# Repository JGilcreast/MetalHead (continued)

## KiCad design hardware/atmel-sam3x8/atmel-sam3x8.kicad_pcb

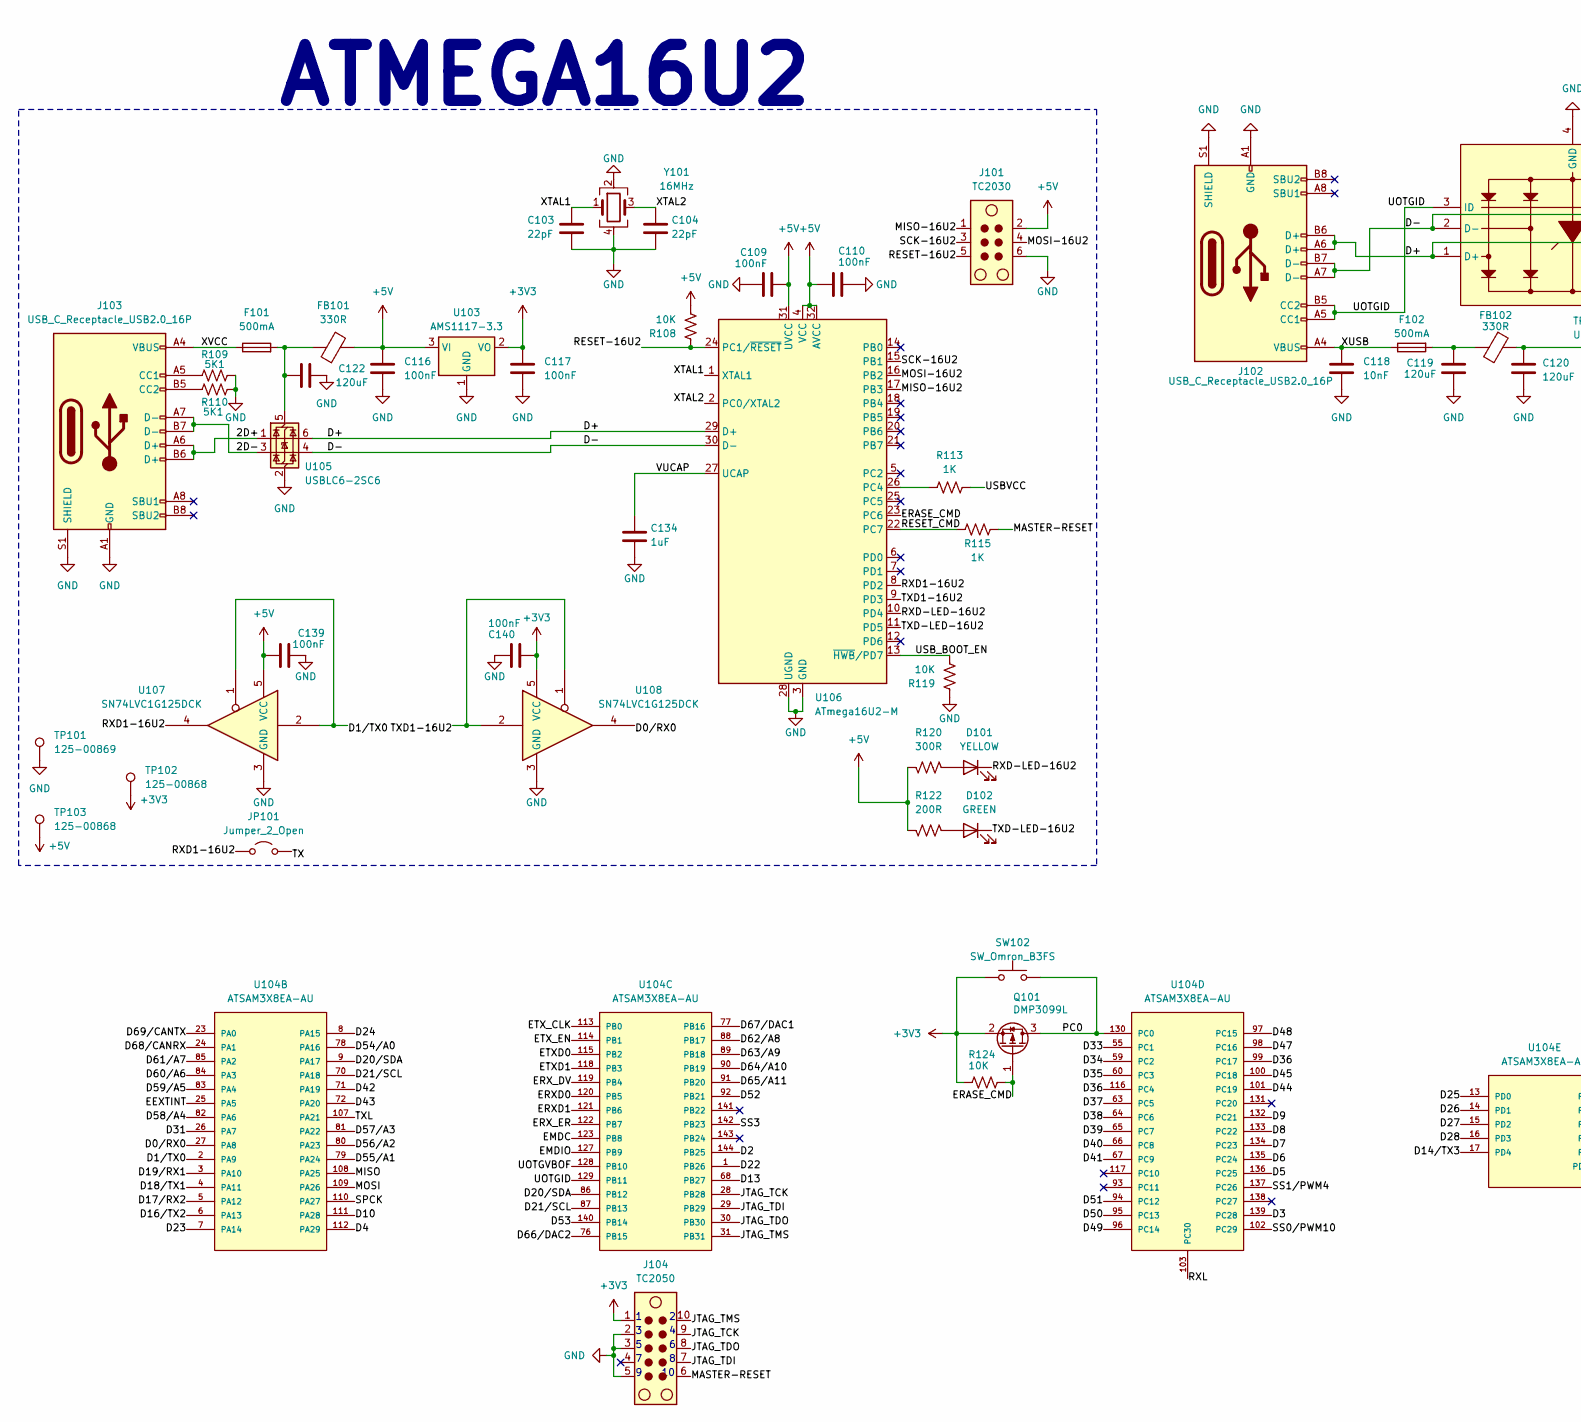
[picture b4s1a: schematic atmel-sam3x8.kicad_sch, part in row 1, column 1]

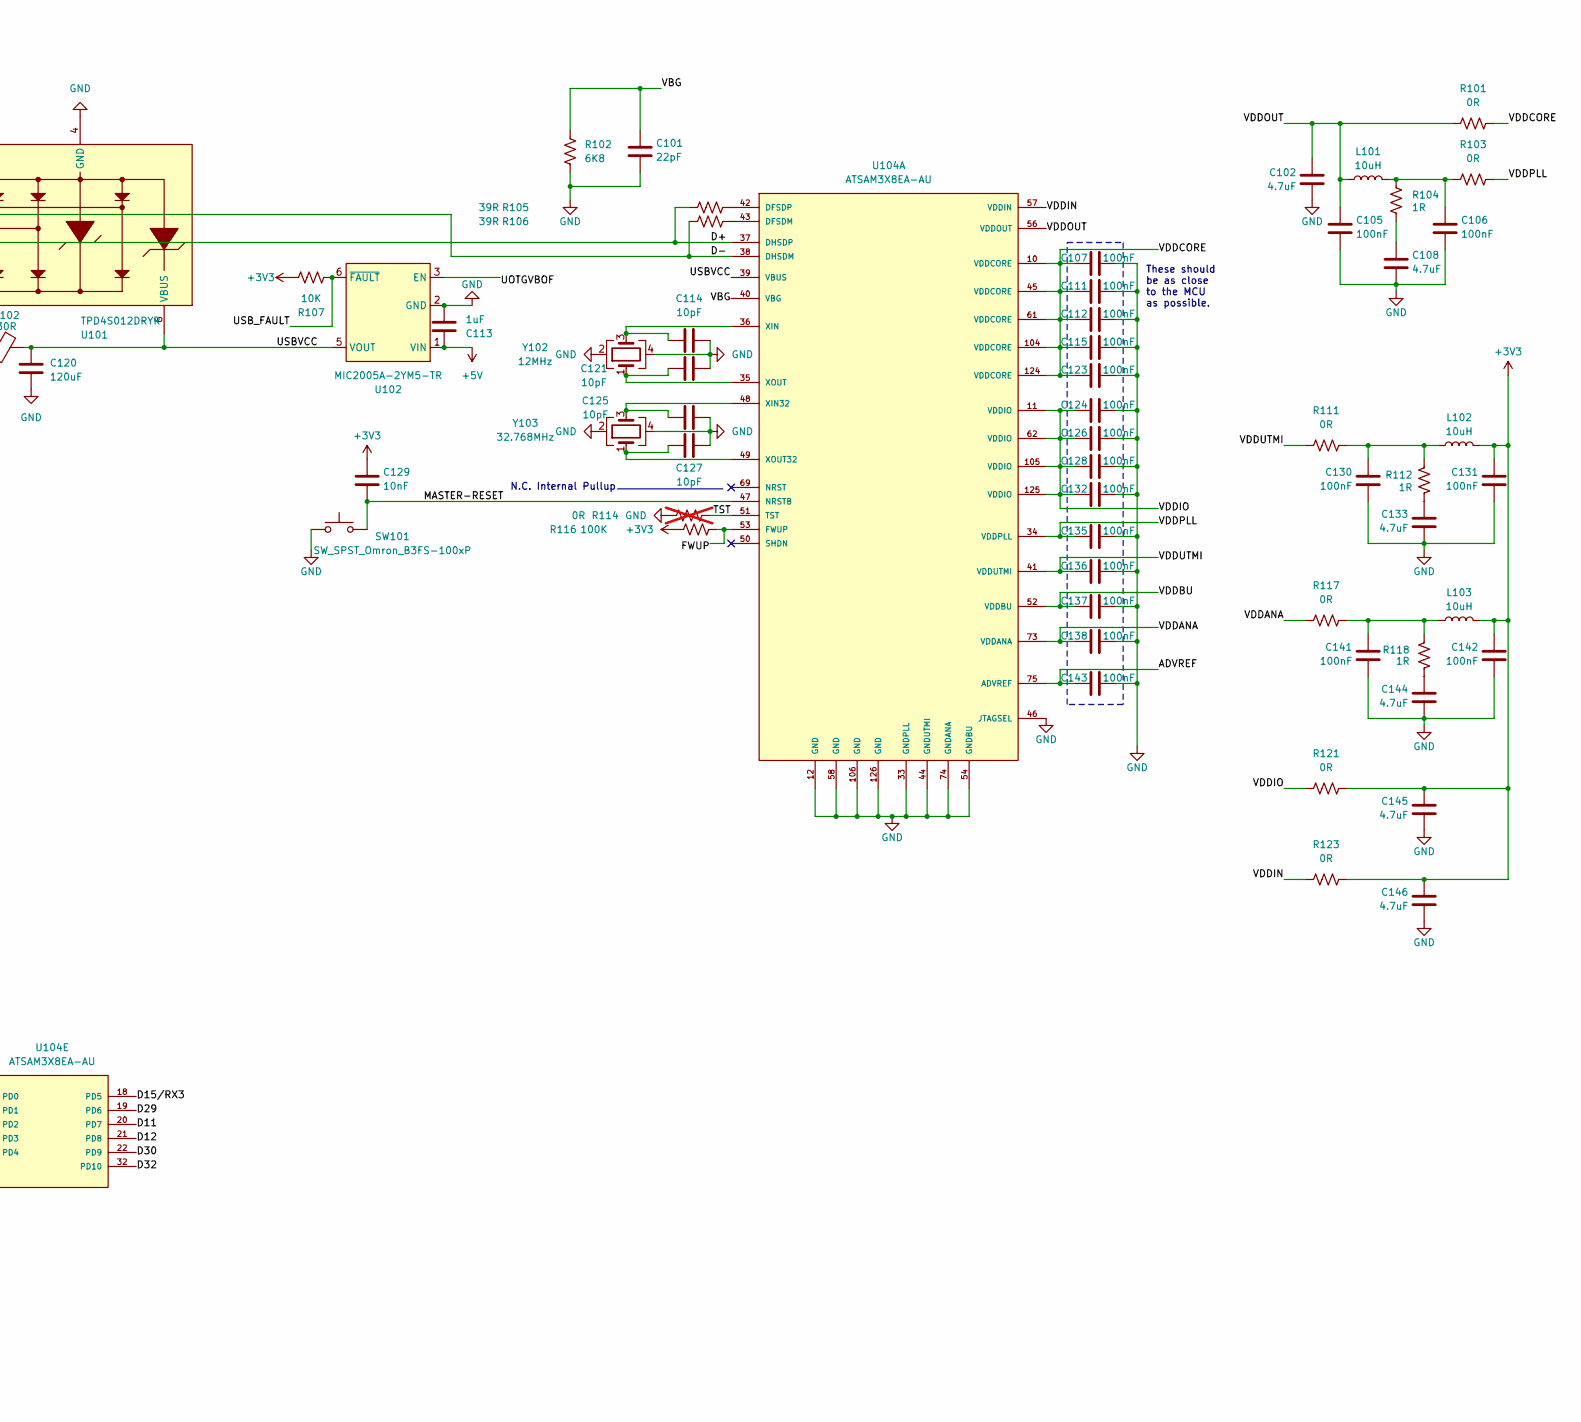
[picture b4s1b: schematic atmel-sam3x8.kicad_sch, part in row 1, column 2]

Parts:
C101, C103, C104: 22pF; C_0805_2012Metric
C102, C108, C133, C144, C145, C146: 4.7uF; C_0805_2012Metric
C105, C106, C107, C109, C110, C111, C112, C115, C116, C117, C123, C124, C126, C128, C130, C131, C132, C135, C136, C137, C138, C139, C140, C141, C142, C143: 100nF; C_0805_2012Metric
C113, C134: 1uF; C_0805_2012Metric
C114, C121, C125, C127: 10pF; C_0805_2012Metric
C118, C129: 10nF; C_0805_2012Metric
C119, C120, C122: 120uF; C_0805_2012Metric
D101: YELLOW; LED_1206_3216Metric
D102: GREEN; LED_1206_3216Metric
F101, F102: 500mA; Fuse_0805_2012Metric
FB101, FB102: 330R; L_0805_2012Metric
J101: TC2030; Tag-Connect_TC2030-IDC-NL_2x03_P1.27mm_Vertical
J102, J103: USB_C_Receptacle_USB2.0_16P; USB_C_Receptacle_G-Switch_GT-USB-7010ASV
J104: TC2050; Tag-Connect_TC2050-IDC-FP_2x05_P1.27mm_Vertical
JP101: Jumper_2_Open; TestPoint_2Pads_Pitch2.54mm_Drill0.8mm
L101, L102, L103: 10uH; L_0805_2012Metric
Q101: DMP3099L; SOT-23-3
R101, R103, R111, R117, R121, R123: 0R; R_0805_2012Metric
R102: 6K8; R_0805_2012Metric
R104, R112, R118: 1R; R_0805_2012Metric
R105, R106: 39R; R_0805_2012Metric
R107, R108, R119, R124: 10K; R_0805_2012Metric
R109, R110: 5K1; R_0805_2012Metric
R113, R115: 1K; R_0805_2012Metric
R114: 0R; R_0805_2012Metric; not fitted
R116: 100K; R_0805_2012Metric
R120: 300R; R_0805_2012Metric
R122: 200R; R_0805_2012Metric
SW101: SW_SPST_Omron_B3FS-100xP; SW_SPST_EVQPE1
SW102: SW_Omron_B3FS; SW_SPST_Omron_B3FS-100xP
TP101: 125-00869; TestPoint_Keystone_5000-5004_Miniature
TP102, TP103: 125-00868; TestPoint_Keystone_5000-5004_Miniature
U101: TPD4S012DRYR; Mouser Part Number 595-TPD4S012DRYR
U102: MIC2005A-2YM5-TR; SOT95P280X145-5N; Mouser Part Number 998-MIC2005A-1YM5TR
U103: AMS1117-3.3; SOT-223-3_TabPin2
U104: ATSAM3X8EA-AU; QFP50P2200X2200X145-144N; PARTREV 11057C
U105: USBLC6-2SC6; SOT-23-6
U106: ATmega16U2-M; QFN-32-1EP_5x5mm_P0.5mm_EP3.6x3.6mm_ThermalVias
U107, U108: SN74LVC1G125DCK; Texas_R-PDSO-G5_DCK-5
Y101: 16MHz; Crystal_SMD_3225-4Pin_3.2x2.5mm
Y102: 12MHz; Crystal_SMD_3225-4Pin_3.2x2.5mm
Y103: 32.768MHz; Crystal_SMD_3225-4Pin_3.2x2.5mm

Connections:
+3V3: C117.1, C129.1, C131.1, C140.1, C142.1, C145.1, C146.1, J104.1, L102.1, L103.1, Q101.2 (S), R107.2, R116.1, R121.2, R123.2, R124.2, SW102.1, TP102.1, U103.2 (VO), U108.5 (VCC)
+5V: C109.1, C110.1, C113.1, C116.1, C139.1, FB101.2, J101.2, R108.2, R120.2, R122.2, TP103.1, U102.1 (VIN), U103.3 (VI), U106.4 (VCC), U106.31 (UVCC), U106.32 (AVCC), U107.5 (VCC)
/2D+: J103.A6 (D+), J103.B6 (D+), U105.1 (I/O1)
/2D-: J103.A7 (D-), J103.B7 (D-), U105.3 (I/O2)
/ADVREF: C143.1, U104.75 (ADVREF)
/D0/RX0: U104.27 (PA8), U108.4
/D1/TX0: U104.2 (PA9), U107.1, U107.2
/D2: U104.144 (PB25)
/D3: U104.139 (PC28)
/D4: U104.112 (PA29)
/D5: U104.136 (PC25)
/D6: U104.135 (PC24)
/D7: U104.134 (PC23)
/D8: U104.133 (PC22)
/D9: U104.132 (PC21)
/D10: U104.111 (PA28)
/D11: U104.20 (PD7)
/D12: U104.21 (PD8)
/D13: U104.68 (PB27)
/D14/TX3: U104.17 (PD4)
/D15/RX3: U104.18 (PD5)
/D16/TX2: U104.6 (PA13)
/D17/RX2: U104.5 (PA12)
/D18/TX1: U104.4 (PA11)
/D19/RX1: U104.3 (PA10)
/D20/SDA: U104.9 (PA17), U104.86 (PB12)
/D21/SCL: U104.70 (PA18), U104.87 (PB13)
/D22: U104.1 (PB26)
/D23: U104.7 (PA14)
/D24: U104.8 (PA15)
/D25: U104.13 (PD0)
/D26: U104.14 (PD1)
/D27: U104.15 (PD2)
/D28: U104.16 (PD3)
/D29: U104.19 (PD6)
/D30: U104.22 (PD9)
/D31: U104.26 (PA7)
/D32: U104.32 (PD10)
/D33: U104.55 (PC1)
/D34: U104.59 (PC2)
/D35: U104.60 (PC3)
/D36: U104.99 (PC17), U104.116 (PC4)
/D37: U104.63 (PC5)
/D38: U104.64 (PC6)
/D39: U104.65 (PC7)
/D40: U104.66 (PC8)
/D41: U104.67 (PC9)
/D42: U104.71 (PA19)
/D43: U104.72 (PA20)
/D44: U104.101 (PC19)
/D45: U104.100 (PC18)
/D47: U104.98 (PC16)
/D48: U104.97 (PC15)
/D49: U104.96 (PC14)
/D50: U104.95 (PC13)
/D51: U104.94 (PC12)
/D52: U104.92 (PB21)
/D53: U104.140 (PB14)
/D54/A0: U104.78 (PA16)
/D55/A1: U104.79 (PA24)
/D56/A2: U104.80 (PA23)
/D57/A3: U104.81 (PA22)
/D58/A4: U104.82 (PA6)
/D59/A5: U104.83 (PA4)
/D60/A6: U104.84 (PA3)
/D61/A7: U104.85 (PA2)
/D62/A8: U104.88 (PB17)
/D63/A9: U104.89 (PB18)
/D64/A10: U104.90 (PB19)
/D65/A11: U104.91 (PB20)
/D66/DAC2: U104.76 (PB15)
/D67/DAC1: U104.77 (PB16)
/D68/CANRX: U104.24 (PA1)
/D69/CANTX: U104.23 (PA0)
/D+: J102.A5 (CC1), J102.A6 (D+), J102.A7 (D-), J102.B5 (CC2), J102.B6 (D+), J102.B7 (D-), R105.2, R106.2, U101.1 (D+), U101.2 (D-), U101.3 (ID), U104.37 (DHSDP), U104.38 (DHSDM), U104.129 (PB11), U105.4 (I/O2), U105.6 (I/O1), U106.29 (D+), U106.30 (D-)
/EEXTINT: U104.25 (PA5)
/EMDC: U104.123 (PB8)
/EMDIO: U104.127 (PB9)
/ERASE_CMD: Q101.1 (G), R124.1, U106.23 (PC6)
/ERXD0: U104.120 (PB5)
/ERXD1: U104.121 (PB6)
/ERX_DV: U104.119 (PB4)
/ERX_ER: U104.122 (PB7)
/ETXD0: U104.115 (PB2)
/ETXD1: U104.118 (PB3)
/ETX_CLK: U104.113 (PB0)
/ETX_EN: U104.114 (PB1)
/FWUP: R116.2, U104.53 (FWUP)
/JTAG_TCK: J104.9, U104.28 (PB28)
/JTAG_TDI: J104.7, U104.29 (PB29)
/JTAG_TDO: J104.8, U104.30 (PB30)
/JTAG_TMS: J104.10, U104.31 (PB31)
/MASTER-RESET: C129.2, J104.6, R115.2, SW101.2, U104.47 (NRSTB)
/MISO: U104.108 (PA25)
/MISO-16U2: J101.1, U106.17 (PB3)
/MOSI: U104.109 (PA26)
/MOSI-16U2: J101.4, U106.16 (PB2)
/PC0: Q101.3 (D), SW102.2, U104.130 (PC0)
/RESET-16U2: J101.5, R108.1, U106.24 (PC1/~RESET)
/RESET_CMD: R115.1, U106.22 (PC7)
/RXD1-16U2: JP101.1 (A), U106.8 (PD2), U107.4
/RXD-LED-16U2: D101.1 (K), U106.10 (PD4)
/RXL: U104.103 (PC30)
/SCK-16U2: J101.3, U106.15 (PB1)
/SPCK: U104.110 (PA27)
/SS0/PWM10: U104.102 (PC29)
/SS1/PWM4: U104.137 (PC26)
/SS3: U104.142 (PB23)
/TST: R114.1, U104.51 (TST)
/TX: JP101.2 (B)
/TXD1-16U2: U106.9 (PD3), U108.1, U108.2
/TXD-LED-16U2: D102.1 (K), U106.11 (PD5)
/TXL: U104.107 (PA21)
/UOTGVBOF: U102.3 (EN), U104.128 (PB10)
/USBVCC: C120.1, FB102.1, R113.2, U101.6 (VBUS), U102.5 (VOUT), U104.39 (VBUS)
/USB_BOOT_EN: R119.2, U106.13 (~HWB/PD7)
/USB_FAULT: R107.1, U102.6 (~FAULT)
/VBG: C101.1, R102.1, U104.40 (VBG)
/VDDANA: C138.1, R117.1, U104.73 (VDDANA)
/VDDBU: C137.1, U104.52 (VDDBU)
/VDDCORE: C107.1, C111.1, C112.1, C115.1, C123.1, R101.2, U104.10 (VDDCORE), U104.45 (VDDCORE), U104.61 (VDDCORE), U104.104 (VDDCORE), U104.124 (VDDCORE)
/VDDIN: R123.1, U104.57 (VDDIN)
/VDDIO: C124.1, C126.1, C128.1, C132.1, R121.1, U104.11 (VDDIO), U104.62 (VDDIO), U104.105 (VDDIO), U104.125 (VDDIO)
/VDDOUT: C102.1, C105.1, L101.2, R101.1, U104.56 (VDDOUT)
/VDDPLL: C135.1, R103.2, U104.34 (VDDPLL)
/VDDUTMI: C136.1, R111.1, U104.41 (VDDUTMI)
/VUCAP: C134.1, U106.27 (UCAP)
/XTAL1: C103.1, U106.1 (XTAL1), Y101.1
/XTAL2: C104.1, U106.2 (PC0/XTAL2), Y101.3
/XUSB: C118.1, F102.1, J102.A4 (VBUS), J102.A9 (VBUS), J102.B4 (VBUS), J102.B9 (VBUS)
/XVCC: F101.1, J103.A4 (VBUS), J103.A9 (VBUS), J103.B4 (VBUS), J103.B9 (VBUS)
GND: C101.2, C102.2, C103.2, C104.2, C105.2, C106.2, C107.2, C108.2, C109.2, C110.2, C111.2, C112.2, C113.2, C114.2, C115.2, C116.2, C117.2, C118.2, C119.1, C120.2, C121.2, C122.1, C123.2, C124.2, C125.2, C126.2, C127.2, C128.2, C130.2, C131.2, C132.2, C133.2, C134.2, C135.2, C136.2, C137.2, C138.2, C139.2, C140.2, C141.2, C142.2, C143.2, C144.2, C145.2, C146.2, J101.6, J102.A1 (GND), J102.A12 (GND), J102.B1 (GND), J102.B12 (GND), J102.S1 (SHIELD), J103.A1 (GND), J103.A12 (GND), J103.B1 (GND), J103.B12 (GND), J103.S1 (SHIELD), J104.2, J104.3, J104.5, R102.2, R109.1, R110.1, R114.2, R119.1, SW101.1, TP101.1, U101.4 (GND), U102.2 (GND), U103.1 (GND), U104.12 (GND), U104.33 (GNDPLL), U104.44 (GNDUTMI), U104.46 (JTAGSEL), U104.54 (GNDBU), U104.58 (GND), U104.74 (GNDANA), U104.106 (GND), U104.126 (GND), U105.2 (GND), U106.3 (GND), U106.28 (UGND), U106.33 (GND), U107.3 (GND), U108.3 (GND), Y101.2, Y101.4, Y102.2, Y102.4, Y103.2, Y103.4
unnamed: C106.1, L101.1, R103.1, R104.2
unnamed: C108.1, R104.1
unnamed: C119.2, F102.2, FB102.2
unnamed: C130.1, L102.2, R111.2, R112.2
unnamed: C133.1, R112.1
unnamed: C141.1, L103.2, R117.2, R118.2
unnamed: C144.1, R118.1
unnamed: D101.2 (A), R120.1
unnamed: D102.2 (A), R122.1
unnamed: J103.A5 (CC1), R109.2
unnamed: J103.B5 (CC2), R110.2
unnamed: R106.1, U104.43 (DFSDM)
unnamed: R105.1, U104.42 (DFSDP)
unnamed: C125.1, U104.48 (XIN32), Y103.3
unnamed: C114.1, U104.36 (XIN), Y102.3
unnamed: C127.1, U104.49 (XOUT32), Y103.1
unnamed: C121.1, U104.35 (XOUT), Y102.1
unnamed: C122.2, F101.2, FB101.1, U105.5 (VBUS)
unnamed: R113.1, U106.26 (PC4)

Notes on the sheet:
These should be as close to the MCU as possible.
ATMEGA16U2
N.C. Internal Pullup

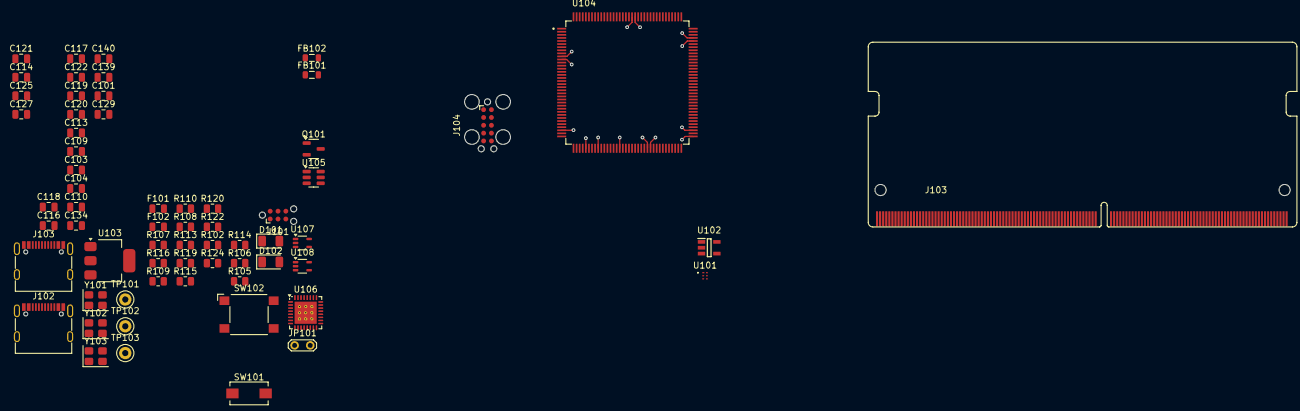
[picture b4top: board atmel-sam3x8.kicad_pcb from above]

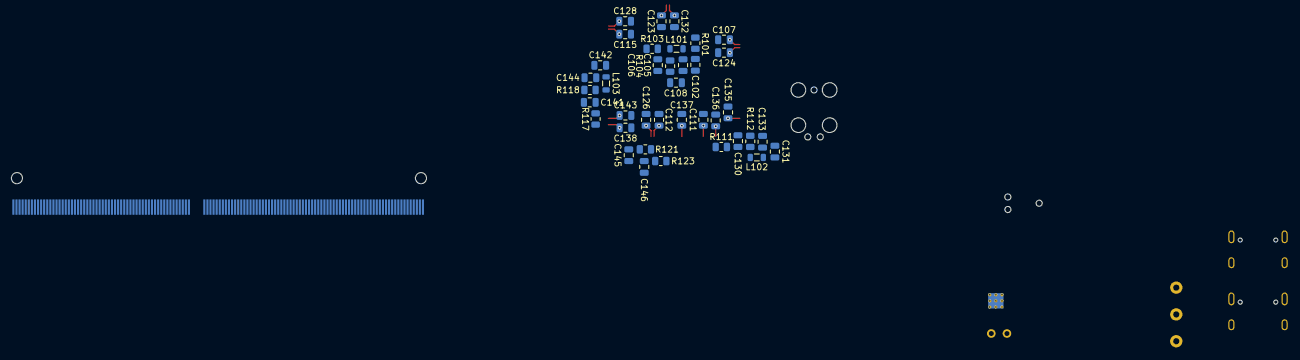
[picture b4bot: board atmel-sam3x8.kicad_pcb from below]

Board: 2 copper layers, 102 parts (38 on the bottom side), 66 nets.

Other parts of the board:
J103#2: SODIMM DDR4 EDGE; SODIMM_DDR4_EDGE

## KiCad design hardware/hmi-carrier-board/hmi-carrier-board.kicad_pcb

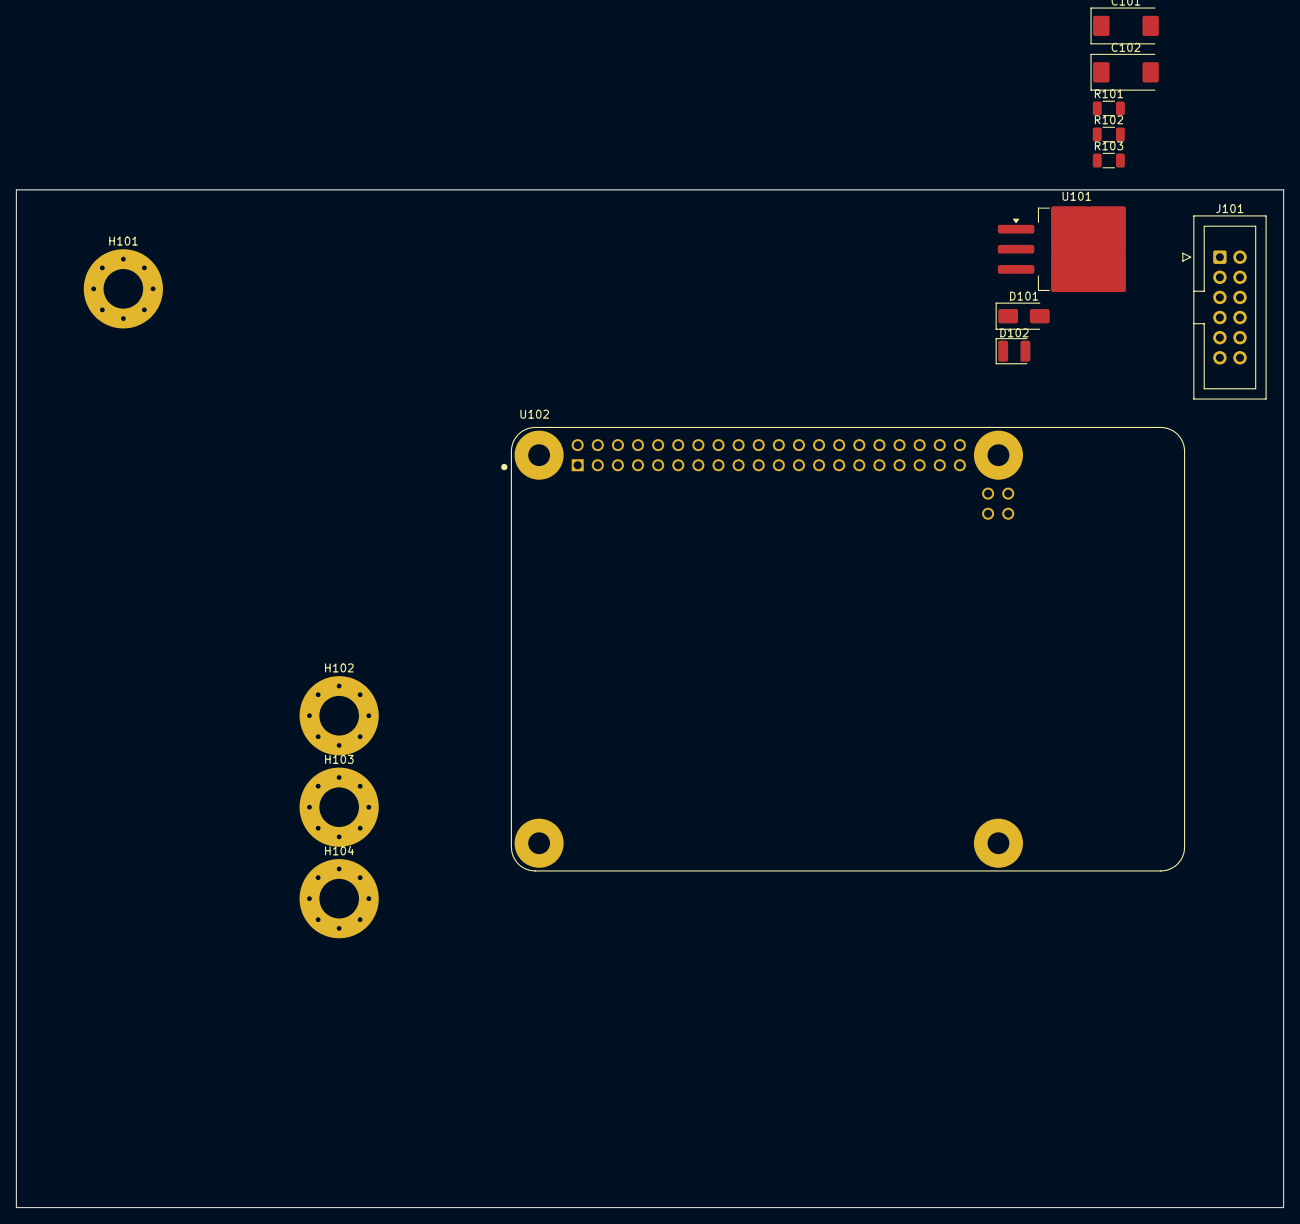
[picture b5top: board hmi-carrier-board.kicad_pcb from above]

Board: 2 copper layers, 160.0 x 128.5 mm, 14 parts (0 on the bottom side), 7 nets, no tracks yet.

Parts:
C101, C102: 10uF 50V; CP_EIA-7343-31_Kemet-D
D101: 1N4002 M2; D_SMA
D102: WHITE; LED_1210_3225Metric
H101, H102, H103, H104: MountingHole_Pad; MountingHole_5mm_Pad_Via
J101: Conn_02x06_Odd_Even; IDC-Header_2x06_P2.54mm_Vertical
R101: 300R; R_1206_3216Metric
R102: 900R; R_1206_3216Metric
R103: 200R; R_1206_3216Metric
U101: LM1084-ADJ; TO-263-3_TabPin2
U102: RASPBERRY_PI_4B_4GB; MODULE_RASPBERRY_PI_4B_4GB

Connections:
+5V: C102.1, D101.2 (A), D102.2 (A), R101.1, U101.2 (VO), U102.2 (5V), U102.4 (5V__1)
+24V: C101.1, D101.1 (K), J101.3, J101.4, U101.3 (VI)
/RX: J101.8, U102.10 (GPIO15/RXD0)
/TX: J101.7, U102.8 (GPIO14/TXD0)
GND: C101.2, C102.2, H101.1, H102.1, H103.1, H104.1, J101.1, J101.2, J101.5, J101.6, J101.9, J101.10, J101.12, R102.2, R103.1, U102.6 (GND), U102.9 (GND__1), U102.14 (GND__2), U102.20 (GND__3), U102.25 (GND__4), U102.30 (GND__5), U102.34 (GND__6), U102.39 (GND__7), U102.S1 (SHIELD), U102.S2 (SHIELD__1), U102.S3 (SHIELD__2), U102.S4 (SHIELD__3)
unnamed: D102.1 (K), R103.2
unnamed: R101.2, R102.1, U101.1 (ADJ)

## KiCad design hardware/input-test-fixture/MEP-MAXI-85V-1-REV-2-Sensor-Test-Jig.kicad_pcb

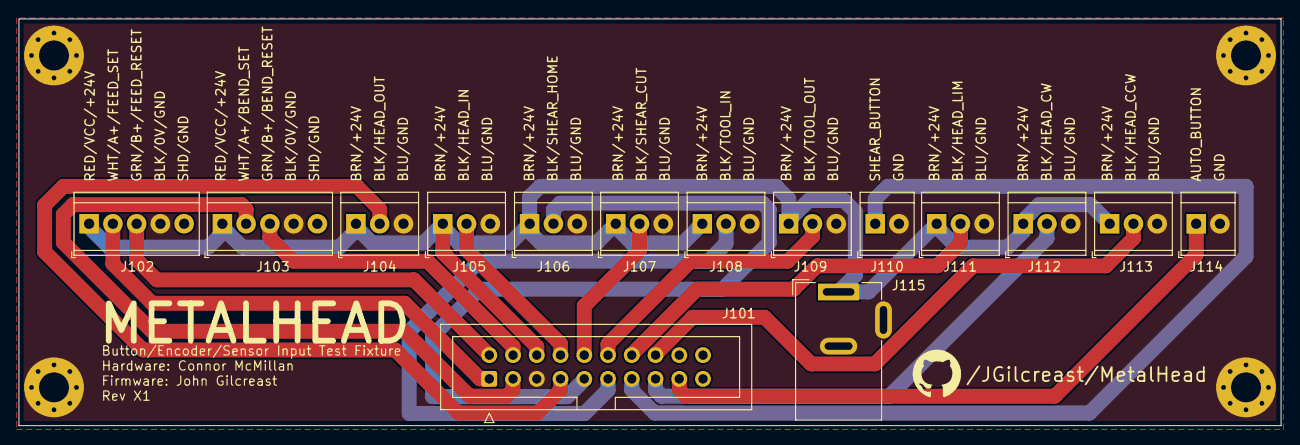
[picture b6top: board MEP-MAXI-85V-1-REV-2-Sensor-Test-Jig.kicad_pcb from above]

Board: 2 copper layers, 135.0 x 43.5 mm, 19 parts (0 on the bottom side), 17 nets.

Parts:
H101, H102, H103, H104: MountingHole_Pad; MountingHole_3.2mm_M3_Pad_Via
J101: Conn_02x10_Odd_Even; IDC-Header_2x10_P2.54mm_Vertical
J102, J103: Screw_Terminal_01x05; TerminalBlock_TE_282834-5_1x05_P2.54mm_Horizontal
J104, J105, J106, J107, J108, J109, J111, J112, J113: Screw_Terminal_01x03; TerminalBlock_TE_282834-3_1x03_P2.54mm_Horizontal
J110, J114: Screw_Terminal_01x02; TerminalBlock_TE_282834-2_1x02_P2.54mm_Horizontal
J115: Barrel_Jack_MountingPin; BarrelJack_Wuerth_6941xx301002

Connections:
24VRAW: J101.6, J102.1, J103.1, J104.1, J105.1, J106.1, J107.1, J108.1, J109.1, J111.1, J112.1, J113.1, J115.1
/AUTO_BUTTON: J101.17, J114.1
/ENCODER_BEND_RESET: J101.4, J103.3
/ENCODER_BEND_SET: J101.3, J103.2
/ENCODER_FEED_RESET: J101.2, J102.3
/ENCODER_FEED_SET: J101.1, J102.2
/PROXIMITY_HEAD_CCW: J101.16, J113.2
/PROXIMITY_HEAD_CW: J101.15, J112.2
/PROXIMITY_HEAD_IN: J101.8, J105.2
/PROXIMITY_HEAD_LIM: J101.14, J111.2
/PROXIMITY_HEAD_OUT: J101.7, J104.2
/PROXIMITY_SHEAR_CUT: J101.10, J107.2
/PROXIMITY_SHEAR_HOME: J101.9, J106.2
/PROXIMITY_TOOL_IN: J101.11, J108.2
/PROXIMITY_TOOL_OUT: J101.12, J109.2
/SHEAR_BUTTON: J101.13, J110.1
GND: H101.1, H102.1, H103.1, H104.1, J101.5, J102.4, J103.4, J104.3, J105.3, J106.3, J107.3, J108.3, J109.3, J110.2, J111.3, J112.3, J113.3, J114.2, J115.2, J115.3 (MountPin)

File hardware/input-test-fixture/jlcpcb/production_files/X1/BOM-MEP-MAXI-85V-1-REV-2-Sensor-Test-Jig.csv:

Comment,Designator,Footprint,LCSC,Quantity
Screw_Terminal_01x03,J105,TerminalBlock_TE_282834-3_1x03_P2.54mm_Horizontal,,1
Screw_Terminal_01x03,J107,TerminalBlock_TE_282834-3_1x03_P2.54mm_Horizontal,,1
Screw_Terminal_01x02,J114,TerminalBlock_TE_282834-2_1x02_P2.54mm_Horizontal,,1
Screw_Terminal_01x03,J111,TerminalBlock_TE_282834-3_1x03_P2.54mm_Horizontal,,1
Screw_Terminal_01x02,J110,TerminalBlock_TE_282834-2_1x02_P2.54mm_Horizontal,,1
Screw_Terminal_01x03,J109,TerminalBlock_TE_282834-3_1x03_P2.54mm_Horizontal,,1
Screw_Terminal_01x05,J103,TerminalBlock_TE_282834-5_1x05_P2.54mm_Horizontal,,1
Screw_Terminal_01x03,J112,TerminalBlock_TE_282834-3_1x03_P2.54mm_Horizontal,,1
Barrel_Jack_MountingPin,J115,BarrelJack_Wuerth_6941xx301002,,1
Conn_02x10_Odd_Even,J101,IDC-Header_2x10_P2.54mm_Vertical,,1
Screw_Terminal_01x03,J108,TerminalBlock_TE_282834-3_1x03_P2.54mm_Horizontal,,1
Screw_Terminal_01x05,J102,TerminalBlock_TE_282834-5_1x05_P2.54mm_Horizontal,,1
Screw_Terminal_01x03,J104,TerminalBlock_TE_282834-3_1x03_P2.54mm_Horizontal,,1
Screw_Terminal_01x03,J113,TerminalBlock_TE_282834-3_1x03_P2.54mm_Horizontal,,1
Screw_Terminal_01x03,J106,TerminalBlock_TE_282834-3_1x03_P2.54mm_Horizontal,,1

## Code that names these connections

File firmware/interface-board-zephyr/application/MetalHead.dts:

/ {
	aliases {
		eeprom-0 = &at24_eeprom_0;
	};

	// Solenoids
	shear_cut: shear_cut {
		compatible = "gpio";
		gpios = <&piob 26 0>;
		label = "SHEAR_CUT";
	};
	shear_home: shear_home {
		compatible = "gpio";
		gpios = <&pioa 14 0>;
		label = "SHEAR_HOME";
	};
	tool_out: tool_out {
		compatible = "gpio";
		gpios = <&pioa 15 0>;
		label = "TOOL_OUT";
	};
	tool_in: tool_in {
		compatible = "gpio";
		gpios = <&piod 0 0>;
		label = "TOOL_IN";
	};
	feed_forward: feed_forward {
		compatible = "gpio";
		gpios = <&piod 1 0>;
		label = "FEED_FORWARD";
	};
	feed_reverse: feed_reverse {
		compatible = "gpio";
		gpios = <&piod 2 0>;
		label = "FEED_REVERSE";
	};
	head_cw: head_cw {
		compatible = "gpio";
		gpios = <&piod 3 0>;
		label = "HEAD_CW";
	};
	head_ccw: head_ccw {
		compatible = "gpio";
		gpios = <&piod 6 0>;
		label = "HEAD_CCW";
	};
	head_out: head_out {
		compatible = "gpio";
		gpios = <&piod 9 0>;
		label = "HEAD_OUT";
	};
	head_in: head_in {
		compatible = "gpio";
		gpios = <&pioa 7 0>;
		label = "HEAD_IN";
	};

	// Encoders
	encoder_feed_set: encoder_feed_set {
		compatible = "gpio";
		gpios = <&piod 10 0>;
		label = "ENCODER_FEED_SET";
	};
	encoder_feed_reset: encoder_feed_reset {
		compatible = "gpio";
		gpios = <&pioc 1 0>;
		label = "ENCODER_FEED_RESET";
	};
	encoder_bend_set: encoder_bend_set {
		compatible = "gpio";
		gpios = <&pioc 2 0>;
		label = "ENCODER_BEND_SET";
	};
	encoder_bend_reset: encoder_bend_reset {
		compatible = "gpio";
		gpios = <&pioc 3 0>;
		label = "ENCODER_BEND_RESET";
	};

	// Proximity sensors
	proximity_head_out: proximity_head_out {
		compatible = "gpio";
		gpios = <&pioc 4 0>;
		label = "PROXIMITY_HEAD_OUT";
	};
	proximity_head_in: proximity_head_in {
		compatible = "gpio";
		gpios = <&pioc 5 0>;
		label = "PROXIMITY_HEAD_IN";
	};
	proximity_shear_home: proximity_shear_home {
		compatible = "gpio";
		gpios = <&pioc 6 0>;
		label = "PROXIMITY_SHEAR_HOME";
	};
	proximity_shear_cut: proximity_shear_cut {
		compatible = "gpio";
		gpios = <&pioc 7 0>;
		label = "PROXIMITY_SHEAR_CUT";
	};
	proximity_tool_in: proximity_tool_in {
		compatible = "gpio";
		gpios = <&pioc 8 0>;
		label = "PROXIMITY_TOOL_IN";
	};
	proximity_tool_out: proximity_tool_out {
		compatible = "gpio";
		gpios = <&pioc 9 0>;
		label = "PROXIMITY_TOOL_OUT";
	};
	proximity_head_limit: proximity_head_limit {
		compatible = "gpio";
		gpios = <&pioa 20 0>;
		label = "PROXIMITY_HEAD_LIMIT";
	};
	proximity_head_cw: proximity_head_cw {
		compatible = "gpio";
		gpios = <&pioc 19 0>;
		label = "PROXIMITY_HEAD_CW";
	};
	proximity_head_ccw: proximity_head_ccw {
		compatible = "gpio";
		gpios = <&pioc 18 0>;
		label = "PROXIMITY_HEAD_CCW";
	};

	// Buttons
	shear_button: shear_button {
		compatible = "gpio";
		gpios = <&pioa 19 0>;
		label = "SHEAR_BUTTON";
	};
	auto_button: auto_button {
		compatible = "gpio";
		gpios = <&pioc 17 0>;
		label = "AUTO_BUTTON";
	};

	// Auxillary
	estop: estop {
		compatible = "gpio";
		gpios = <&pioc 16 1>; // The 1 will invert the active logic
		label = "ESTOP";
	};
	fuse: fuse {
		compatible = "gpio";
		gpios = <&pioc 15 1>; // The 1 will invert the active logic
		label = "FUSE";
	};

	// Power
	vraw24: vraw24 {
		compatible = "gpio";
		gpios = <&pioc 14 0>;
		label = "24VRAW";
	};
	aux24v: aux24v {
		compatible = "gpio";
		gpios = <&pioc 13 0>;
		label = "AUX24V";
	};
};

&twi1 {
	status = "okay";
	clock-frequency = <I2C_BITRATE_FAST>;
	at24_eeprom_0: eeprom@50 {
		compatible = "atmel,at24";
		reg = <0x50>;
		size = <32768>;
		pagesize = <64>;
		address-width = <16>;
		timeout = <5>;
		label = "EEPROM";
	};
	ina226_0: ina226@40 {
		compatible = "ti,ina226";
		reg = <0x40>; // I2C address
		label = "FUSED_GND";
		avg-count = <256>;
		rshunt-micro-ohms = <2000>; // Example: 2 mOhm shunt
		current-lsb-microamps = <457>;  // Example: 457 uA/LSB (15A)
		// Other configurations like bus-voltage-resistor etc.
	};
	ina3221_0: ina3221@41 {
		compatible = "ti,ina3221";
		reg = <0x41>; // I2C address
		label = "TRI-VBUS";
		conv-time-shunt = <4>; // 1.1mS
		conv-time-bus = <4>; // 1.1mS
		avg-mode = <0>; // 1 sample
		enable-channel = <1 1 1>; // Channels 1-3
		shunt-resistors = <2 2 2>; // mOhms for channels 1-3
	};
};

&spi0 {
	w5500: w5500@0 {
		compatible = "wiznet,w5500";
		reg = <0>; // Chip select line
		spi-max-frequency = <8000000>; // Example frequency
		int-gpios = <&piod 7 GPIO_ACTIVE_LOW>; // Replace with your GPIO port and pin
		reset-gpios = <&pioc 25 GPIO_ACTIVE_LOW>; // Replace with your GPIO port and pin
	};
};

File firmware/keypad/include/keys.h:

//
// Created by Connor on 6/23/2025.
//

#ifndef KEYS_H
#define KEYS_H
/* First PCF8575 GPIO I2C Expander - U408 */
#define DISP          0b0000000000000001 // DISPLAY is already defined in Arduino.h
#define COMP          0b0000000000000010
#define INFEED        0b0000000000000100
#define HEAD_POS      0b0000000000001000
#define FORM_TOOL_IN  0b0000000000010000
#define SHEAR         0b0000000000100000
#define PAUSE         0b0000000001000000
#define RUN           0b0000000010000000
#define UP            0b0000000100000000
#define ENTER         0b0000001000000000
#define ONE           0b0000010000000000
#define TWO           0b0000100000000000
#define THREE         0b0001000000000000
#define PLUS          0b0010000000000000
#define LEFT          0b0100000000000000
#define MENU          0b1000000000000000
/* Second PCF8575 GPIO I2C Expander - U407 */
#define RIGHT         0b0000000000000001
#define FOUR          0b0000000000000010
#define FIVE          0b0000000000000100
#define SIX           0b0000000000001000
#define MINUS         0b0000000000010000
#define MEMORY        0b0000000000100000
#define DOWN          0b0000000001000000
#define DECIMAL       0b0000000010000000
#define SEVEN         0b0000000100000000
#define EIGHT         0b0000001000000000
#define NINE          0b0000010000000000
#define ZERO          0b0000100000000000

volatile bool stateDisplay = false;
volatile bool stateComp = false;
volatile bool stateInfeed = false;
volatile bool stateHeadPos = false;
volatile bool stateFormToolIn = false;
volatile bool stateShear = false;
volatile bool statePause = false;
volatile bool stateRun = false;
volatile bool stateUp = false;
volatile bool stateEnter = false;
volatile bool stateOne = false;
volatile bool stateTwo = false;
volatile bool stateThree = false;
volatile bool statePlus = false;
volatile bool stateLeft = false;
volatile bool stateMenu = false;
volatile bool stateRight = false;
volatile bool stateFour = false;
volatile bool stateFive = false;
volatile bool stateSix = false;
volatile bool stateMinus = false;
volatile bool stateMemory = false;
volatile bool stateDown = false;
volatile bool stateDecimal = false;
volatile bool stateSeven = false;
volatile bool stateEight = false;
volatile bool stateNine = false;
volatile bool stateZero = false;

inline void updatePCFStates(uint16_t pcf1Bits, uint16_t pcf2Bits) {
  stateDisplay = bool(pcf1Bits & DISP);
  stateComp = bool(pcf1Bits & COMP);
  stateInfeed = bool(pcf1Bits & INFEED);
  stateHeadPos = bool(pcf1Bits & HEAD_POS);
  stateFormToolIn = bool(pcf1Bits & FORM_TOOL_IN);
  stateShear = bool(pcf1Bits & SHEAR);
  statePause = bool(pcf1Bits & PAUSE);
  stateRun = bool(pcf1Bits & RUN);
  stateUp = bool(pcf1Bits & UP);
  stateEnter = bool(pcf1Bits & ENTER);
  stateOne = bool(pcf1Bits & ONE);
  stateTwo = bool(pcf1Bits & TWO);
  stateThree = bool(pcf1Bits & THREE);
  statePlus = bool(pcf1Bits & PLUS);
  stateLeft = bool(pcf1Bits & LEFT);
  stateMenu = bool(pcf1Bits & MENU);

  stateRight = bool(pcf2Bits & RIGHT);
  stateFour = bool(pcf2Bits & FOUR);
  stateFive = bool(pcf2Bits & FIVE);
  stateSix = bool(pcf2Bits & SIX);
  stateMinus = bool(pcf2Bits & MINUS);
  stateMemory = bool(pcf2Bits & MEMORY);
  stateDown = bool(pcf2Bits & DOWN);
  stateDecimal = bool(pcf2Bits & DECIMAL);
  stateSeven = bool(pcf2Bits & SEVEN);
  stateEight = bool(pcf2Bits & EIGHT);
  stateNine = bool(pcf2Bits & NINE);
  stateZero = bool(pcf2Bits & ZERO);
}

#endif //KEYS_H

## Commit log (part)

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2024-12-28 Initiate Git LFS
    Track *.pdf files using Git LFS
2024-12-28 Initial commit
    Let's do this!
2025-01-04 X1 Release
    Released X1 revision for both the interface board and the input test fixture breakout board.
2025-01-19 Input Test Fixture Rev X2
2025-01-19 Remove KiCAD lock files
    Removed some KiCAD lock files.
2025-01-29 Update .gitattributes
    Updated .gitattributes for videos uploaded.
2025-01-29 Uploaded more pics & vids
    Uploaded more pictures and videos taken by John Gilcreast (JGilcreast).
2025-01-29 Updated Drawings W H V S.pdf
    Updated Drawings W H V S.pdf to include the truth table for the bend & feed encoder multiplexer.
2025-01-30 Updated README.md
    Updated README.md to include some ideas as to what to put in it.
2025-01-30 Update README.md
    Small cosmetic update to README.md
2025-02-04 New Logos
    New simple logos for the project!
2025-02-04 Keypad Firmware
    Placeholder for keypad firmware
2025-02-07 Begin JavaFX HMI
    Began designing the HMI with Scene Builder
2025-02-08 Removed .backup
    Removed the folder containing a backup copy of the HMI software.
2025-02-09 Optimize w/Scene Builder
    Removed GUI assets and optimized them with JavaFX FontIcon. Added a README for editing FMXL files with Scene Builder.
2025-02-09 Update iBOM
    Regenerated iBOM HTML page to align with latest X1 release.
2025-02-09 README.md
    Put a lot of thought to the README.md (a lot more to come) and came up with a reasonable block diagram.
2025-02-09 Updated block diagram
    Updated block diagram to make a little more sense.
2025-02-11 Update README.md
    Updated README.md to include KeypadEvents forwarded from the HMI to the Interface Board when certain keys are pressed.
2025-02-19 Interface Board Test Sketch
    Sketch containing comments and code for testing the interface board.
2025-02-24 Interrupt Queue
    Added a queue to debug interrupts.
2025-03-01 Minor Changes
    Change to formatting and removing an unnecessary if condition
2025-03-09 SBC Carrier Board
    Started to design schematic for the SBC carrier board that will host the HMI application.
2025-03-09 Keypad Schematic
    Started to design the schematic for the keypad. Far from being a X1 rev release.
2025-03-09 ESTOP Bouncing
    Some pictures to show why ESTOP is still bouncing on the output of a CD40106B schmitt trigger inverter.
2025-03-09 HMI cosmetic changes
    Some very minor changes to the HMI application. We are still very far away from an alpha release on the HMI software.
2025-05-04 Remove HMI Carrier Board
    The HMI SBC will be integrated (semi) into the interface board starting on rev X2.
2025-05-04 Scope pics
    Removed some screenshots taken from an oscilloscope that are no longer needed.
2025-06-01 Housekeeping
    Removing large files from LFS.
2025-06-01 Update .gitattributes
    Updated file to prevent uploading new files onto LFS.
2025-06-01 Rev X1
    Finalized rev X1 of the keypad!
2025-06-01 Rev X2
    Finalized rev X2 of the interface board!
    Hopefully there are no major bugs!🤞
2025-06-01 Update .gitignore
    Updated to exclude mp4 files and 85V Maintenance Schedule.pdf
2025-06-01 Update .gitignore
    Updating .gitignore yet again!
2025-06-01 Updated .gitignore
    Yet another .gitignore update again!😞
2025-06-01 Create README.md
    Created a README.md for the video sub directory to list filenames and publicly accessible links for the videos. This is to switch from Github's paid LFS service.
2025-06-01 Update fp-info-cache
2025-06-09 Added outline of a typical run to docs
2025-06-22 Revision X2!
    New and improved revision of the keypad! I fixed issues with the repeater and remote SBC power switch circuit (hopefully🤞). I also integrated the Arduino Nano onto the board (ATMEGA328).
2025-06-29 Initial firmware for keypad
    Some more minor implementations for the keypad to come. Are we still going to send the keystrokes via i2c?? And to what address?? Serial.println() will be good for now.
2025-06-29 Keypad Firmware
    Some house keeping done.
2025-09-06 Initial Arduino API
    Initial Arduino API based firmware for the interface board. This is just the starting point to something bigger.
2025-09-06 Keypad Firmware Updates
    Fixed attachInterrupts for the repeater, consolidated sending to serial into a subroutine (send(const char key[]))and added I2C transmission function.
2025-09-06 Java StatusIndicators Client
    A very crud console client that connects to the interface board, receives a StatusIndicators data structure, and outputs it into the console.
2025-09-06 Update Recipe.h
    Updated Recipe.h. I forgot I was working on this before I committed.
2025-09-26 Rename to Arduino
    Renamed the current interface-board folder under firmware to add 'arduino' in effort to bring in the initial Zephyr RTOS code base.
2025-09-26 Welcome Zephyr RTOS!
    Initial commit that brings in Zephyr RTOS into this project.
2025-10-03 HMI - Crude Edition
    A crude version of the HMI software.
2025-10-03 Client Implementation
    Implemented client code to connect to the HMI to update it in real-time.
2025-10-04 Update .gitignore
    Updated .gitignore to include xml files since JetBrains uses them and so does Maven.
2025-11-15 Remove old code
    Remove old Arduino code
2025-11-15 Added MH Logo
    Add another version of the 'MH' logo in white (#DDDDDD)
2025-11-15 Old PoC code
    Removing old PoC code that has been superseded.
2025-11-15 Updated README.md
    Updated REAME.md. More changes to come as project matures.
2025-11-17 Reimplemented Server
    Reimplemented the server to change it from UDP to an async TCP that handles bi-directional communication more efficiently. It's not 100% done.
2025-11-17 Async TCP Compatibility
    Reimplemented it to make it compatible with the interface board async TCP server. Fixed a lot of GUI issues and added a scrollable text debug log section.
2025-11-18 Added updated opeations doc
2025-12-01 Refactor threading and messaging headers
    Removed semaphores.h and added shape_processor_thread.h to improve thread management. Updated async_tcp_server.h, hmi_client_msg.proto, hmi_server_msg_t.proto, init_current_mon.h, init_net.h, interfa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
2025-12-01 Update protobuf usage and server message enums
    Updated proto file comments for correct protoc usage paths. Modified the State enum in HmiServerMsg.proto and corresponding generated code to add STATE_PROCESS_ACTION and shift enum values. Refactore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
